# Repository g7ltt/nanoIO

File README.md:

# nanoIO
nanoIO CW/RTTY keyer for Arduino Nano

My take on W1HKJ's nanoIO CW/RTTY keyer for FLDigi.

https://oshpark.com/shared_projects/0wyCgFsd

Mount the board component side down on the bottom of the Arduino Nano.

**_From the nanoIO website_**
NanoIO Version 1.3.1 
Authors: David Freese, W1HKJ & Ervin Hegedüs, HA2OS

An FSK / CW interface based on the Arduino nano. Sketch includes an FSK modulator, a CW computer interface, and a CW iambic-A/B keyer.

**FSK Specifications** 
* 5 bit Baudot
* Baud rates 45.45, 50, 75 and 100

**CW Specifications**
* 5 to 100 WPM
* dash/dot ratio adjustable 2.5 to 3.5
* in-line increment decrement WPM using ^ and | characters
* incremental size user adjustable
* PTT signal generated by Arduino

**Both**
* An internal buffer of 200 characters is available for buffered transmit.

**Hardware requirement**
* Arduino nano or compatible
* LTV-827 dual opto-isolator
* 2 620 ohm ¼ watt resistor (should work with 500 < R < 820 ohm)
* 2 0.1uF capacitor
* Suitable connectors to interface to transceiver

More information here http://www.w1hkj.com/files/nanoIO/

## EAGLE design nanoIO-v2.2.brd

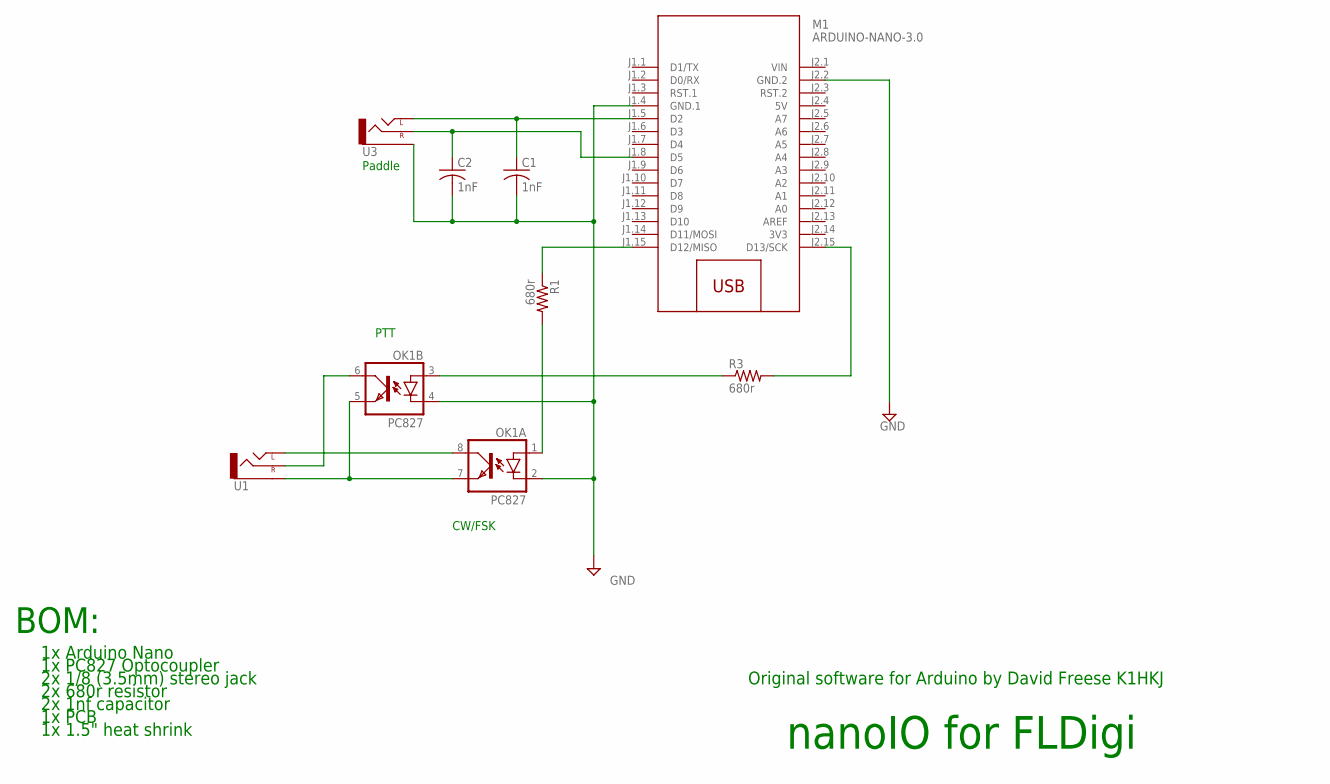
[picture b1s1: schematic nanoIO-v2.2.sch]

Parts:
C1, C2: 1nF; C025-025X050
M1: ARDUINO-NANO-3.0
OK1: PC827; DIL08
R1, R3: 680r; 0204/7
U1, U3: AUDIO-JACKPTH; AUDIO-JACK

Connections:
3V3: M1.J2.14 (3V3)
5V: M1.J2.4 (5V)
GND: C1.2, C2.2, M1.J1.4 (GND.1), M1.J2.2 (GND.2), OK1.2 (C), OK1.4 (C), U3.SLEEVE
unnamed: C1.1, M1.J1.5 (D2), U3.TIP (LEFT)
unnamed: OK1.1 (A), R1.2
unnamed: C2.1, M1.J1.8 (D5), U3.RING (RIGHT)
unnamed: M1.J2.15 (D13/SCK), R3.2
unnamed: M1.J1.15 (D12/MISO), R1.1
unnamed: OK1.5 (EMIT), OK1.7 (EMIT), U1.SLEEVE
unnamed: OK1.8 (COL), U1.TIP (LEFT)
unnamed: OK1.3 (A), R3.1
unnamed: OK1.6 (COL), U1.RING (RIGHT)
VIN: M1.J2.1 (VIN)

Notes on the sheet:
nanoIO for FLDigi
CW/FSK
Paddle
PTT
Original software for Arduino by David Freese K1HKJ
BOM:
1x Arduino Nano
1x PC827 Optocoupler
2x 1/8 (3.5mm) stereo jack
2x 680r resistor
2x 1nf capacitor
1x PCB
1x 1.5" heat shrink

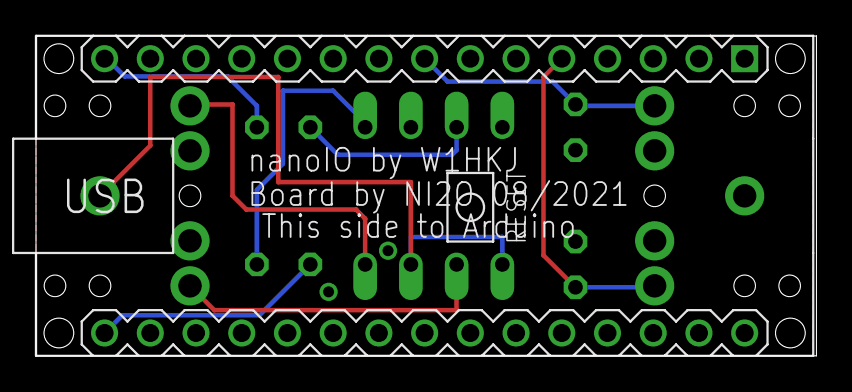
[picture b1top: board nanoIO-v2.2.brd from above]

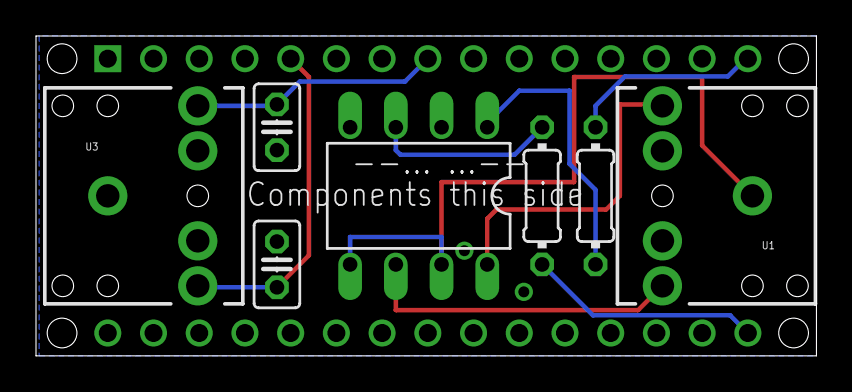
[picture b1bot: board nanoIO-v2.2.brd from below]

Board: 2 copper layers, 43.4 x 17.8 mm, 8 parts (7 on the bottom side), 10 nets.

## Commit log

2021-10-01 Create test

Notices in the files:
parts and their libraries:
SparkFun: Licensing: CC v3.0 Share-Alike You are welcome to use this library for commercial purposes.
diy-modules: Released under the Creative Commons Attribution 4.0 International License: http://creativecommons.org/licenses/by/4.0
